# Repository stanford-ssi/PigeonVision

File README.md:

# PigeonVision

Video downlink for Stanford SSI's IREC rocket. Two fisheye cameras record the flight and send video to the ground for stitching and viewing.

Try the [flight demo](https://stanford-ssi.github.io/PigeonVision/) to see the camera views and stitched panorama.

**Current plan:** two IMX900 cameras at 30 fps, one CM5 and [Yapogee S3](hardware/yapogee-s3/README.md), an ESP32-S3-WROOM-1U DVB-S2 transmitter with RFFC5072A conversion from 2.42 GHz to 1.28 GHz. Keep Ethernet for an E200 fallback and a separate PA/filter board. The ESP32 path has conducted RF/video results; the new converter and PA chain still need schematic capture and hardware testing. Flight channel, bandwidth, power and ground receiver remain open.

- [Hardware](hardware/README.md): system diagram, carrier and RF frontend.
- [Yapogee S3](hardware/yapogee-s3/README.md): transmitter architecture, 5 V interface and waveform candidates.
- [Software](software/README.md): flight and ground tasks.
- [Link budget](calculations/link-budget.xlsx): RF and video bitrate calculations.
- [Simulator](docs/README.md): camera views, flight playback and local setup.

**Next:** capture and review the Yapogee S3 schematic, integrate the carrier interface and PA control, then complete layout and hardware qualification. The system, carrier, RF and software diagrams describe this plan; existing Pico transport measurements remain historical evidence.

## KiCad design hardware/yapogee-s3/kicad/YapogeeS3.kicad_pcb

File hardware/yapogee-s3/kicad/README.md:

# Yapogee S3 KiCad

Open [YapogeeS3.kicad_pro](YapogeeS3.kicad_pro) in KiCad 10. Placement, routing and ground stitching are captured. USB breakout and silkscreen DRC follow-up remains.

| Sheet | Main parts |
| --- | --- |
| Root | USB-C, TPD2EUSB30, CC resistors, JP1 and the castellated edge |
| MCU | WROOM-1U-N16R8, direct host bus, RF control translator, local BOOT/RESET and native USB |
| POWER | TPS62933FDRLR, SRP5030TA-2R2M, TPS7A9001DSKR, TPS22919DCKR |
| RF_FRONT_END | RFFC5072A, TCXO/reference buffer, baluns, filter, SPF5043Z and SMA |

[Design Master](../design-master.xlsx) · [Datasheet PDFs](../datasheets.md) · [BOM](../BOM.csv) · [Interfaces](../interfaces.md)

The project tables include local IO and Power libraries. The IO library includes the module-edge strip symbol, assigned to the paired header/castellation footprint with 12 extra GND anchors. Power rails use global symbols; hierarchy ports carry signals. The BOM covers the captured circuit. Numbering is retained during the direct-host change. GPIO2 is free and castellation 14 is reserved.

Power, direct host GPIO, RF control translation and MCU EN/reset/boot support are captured. RF capture includes matching, PLL loop, reference, supplies and driver. The RF sheet uses A3 for spacing. Design Master contains capacitor screens and loop-model estimates; hardware stability is unmeasured.

J1 carries the closed 55 × 43.18 mm Edge.Cuts outline, R1 outer corners and the Samtec drop-in notch. The 19 mm U.FL harness remains one arc on Dwgs.User. Headers sit 1.60 mm inboard with continuous oval copper lands; retain manual edge soldering and no carrier paste. The JLCPCB JLC04161H-7628 standard 1.6 mm four-layer stackup is entered: 1 oz outer copper, 0.5 oz inner copper.

JP2 BOOT and JP3 RESET are bare, normally-open PCB jumper pads. For manual download, close BOOT during reset. Leave both open for normal operation; briefly short RESET to pull EN to GND. Native USB provides the usual ESP flashing path, without a UART bridge or Pi BOOT control.

## RF and routing

| Network | Populated values |
| --- | --- |
| Input pad | 3 dB nominal; 300 / 18 / 300 |
| Balanced DC blocks | C32/C33 and C59/C60: 100 pF each |
| Mixer output feeds | L3/L4: 7.5 nH each, LQW15AN7N5G80D |
| Driver feed | L2: 100 nH |
| Frequency plan | 3700 MHz LO − 2420 MHz input = 1280 MHz output; spectrum inverted |

Matching uses nominal manufacturer port and passive models. Bias 6 input impedance is unknown; assembled matching, output power and EVM remain unmeasured. Keep balanced connections short and symmetric. L3/L4 may need tuning after assembly.

MODE uses a 10k pullup. EXT_LO and EXT_LO_DEC stay open with the internal LO. The reference divider is nominally 1.2 Vpp before REF_IN loading. The driver uses switched 3.328 V minus switch, resistor and choke drops. Its 3 V characterization is typical; gain, stability and EVM need measurement. [RF plots](../plots/README.md).

| Netclass | Width (mm) | Pair gap (mm) | Coplanar GND gap (mm) |
| --- | ---: | ---: | ---: |
| RF50 | 0.32 | — | 0.25 |
| USB90 | 0.235 | 0.15 | 0.25 |
| RF_MATCH | 0.20 | — | — |
| REF40 | 0.20 | — | — |

RF50 and USB90 use masked L1 traces over continuous L2 GND. Hold the listed GND gaps with the actual copper pours; netclass clearance is only a minimum. RF_MATCH marks short lumped-network connections, not controlled 100/200 Ω lines. Vendor geometry still requires fabrication/CAM confirmation. [Stackup](../stackup.json) · [JLC calculator](https://jlcpcb.com/pcb-impedance-calculator)

Continuous RF wires use automatic net names with explicit netclass patterns. Recheck assignments after reannotation. USB_P/N and MCU UD_P/N are recognized differential pairs on both sides of R3/R4. REF40 is a short clock interconnect default, without an impedance target. Bypass captions assign each capacitor pair to its physical supply pin.

[JLC fabrication and routing rules](YapogeeS3.kicad_dru) are loaded with RF50, RF_MATCH, REF40, USB90 and power netclasses. RF50 and USB90 have explicit 0.25 mm clearance to GND. USB retains 0.15 mm pair spacing. Standard through vias only; USB breakout spacing and small existing silk still need DRC review.

Use netclass widths. Supply defaults are 0.75 mm for 5 V, 0.50 mm for 3V3_MAIN and 0.30 mm for RF/driver supplies; use pours where practical. These widths are starting values, not current or thermal qualifications. Default vias are 0.60/0.30 mm. New zones use netclass clearances; maintain the calculated 0.25 mm GND gaps along RF50 and USB90.

Ground stitching uses 0.50/0.20 mm vias across the board, with closer placement along RF paths and the shield. Minimum via diameter is 0.45 mm with a 0.125 mm annulus; via-to-via hole spacing is 0.20 mm. Component-hole spacing remains 0.45 mm. Refill and rerun DRC after routing changes. Stitch placement is not an EM validation.

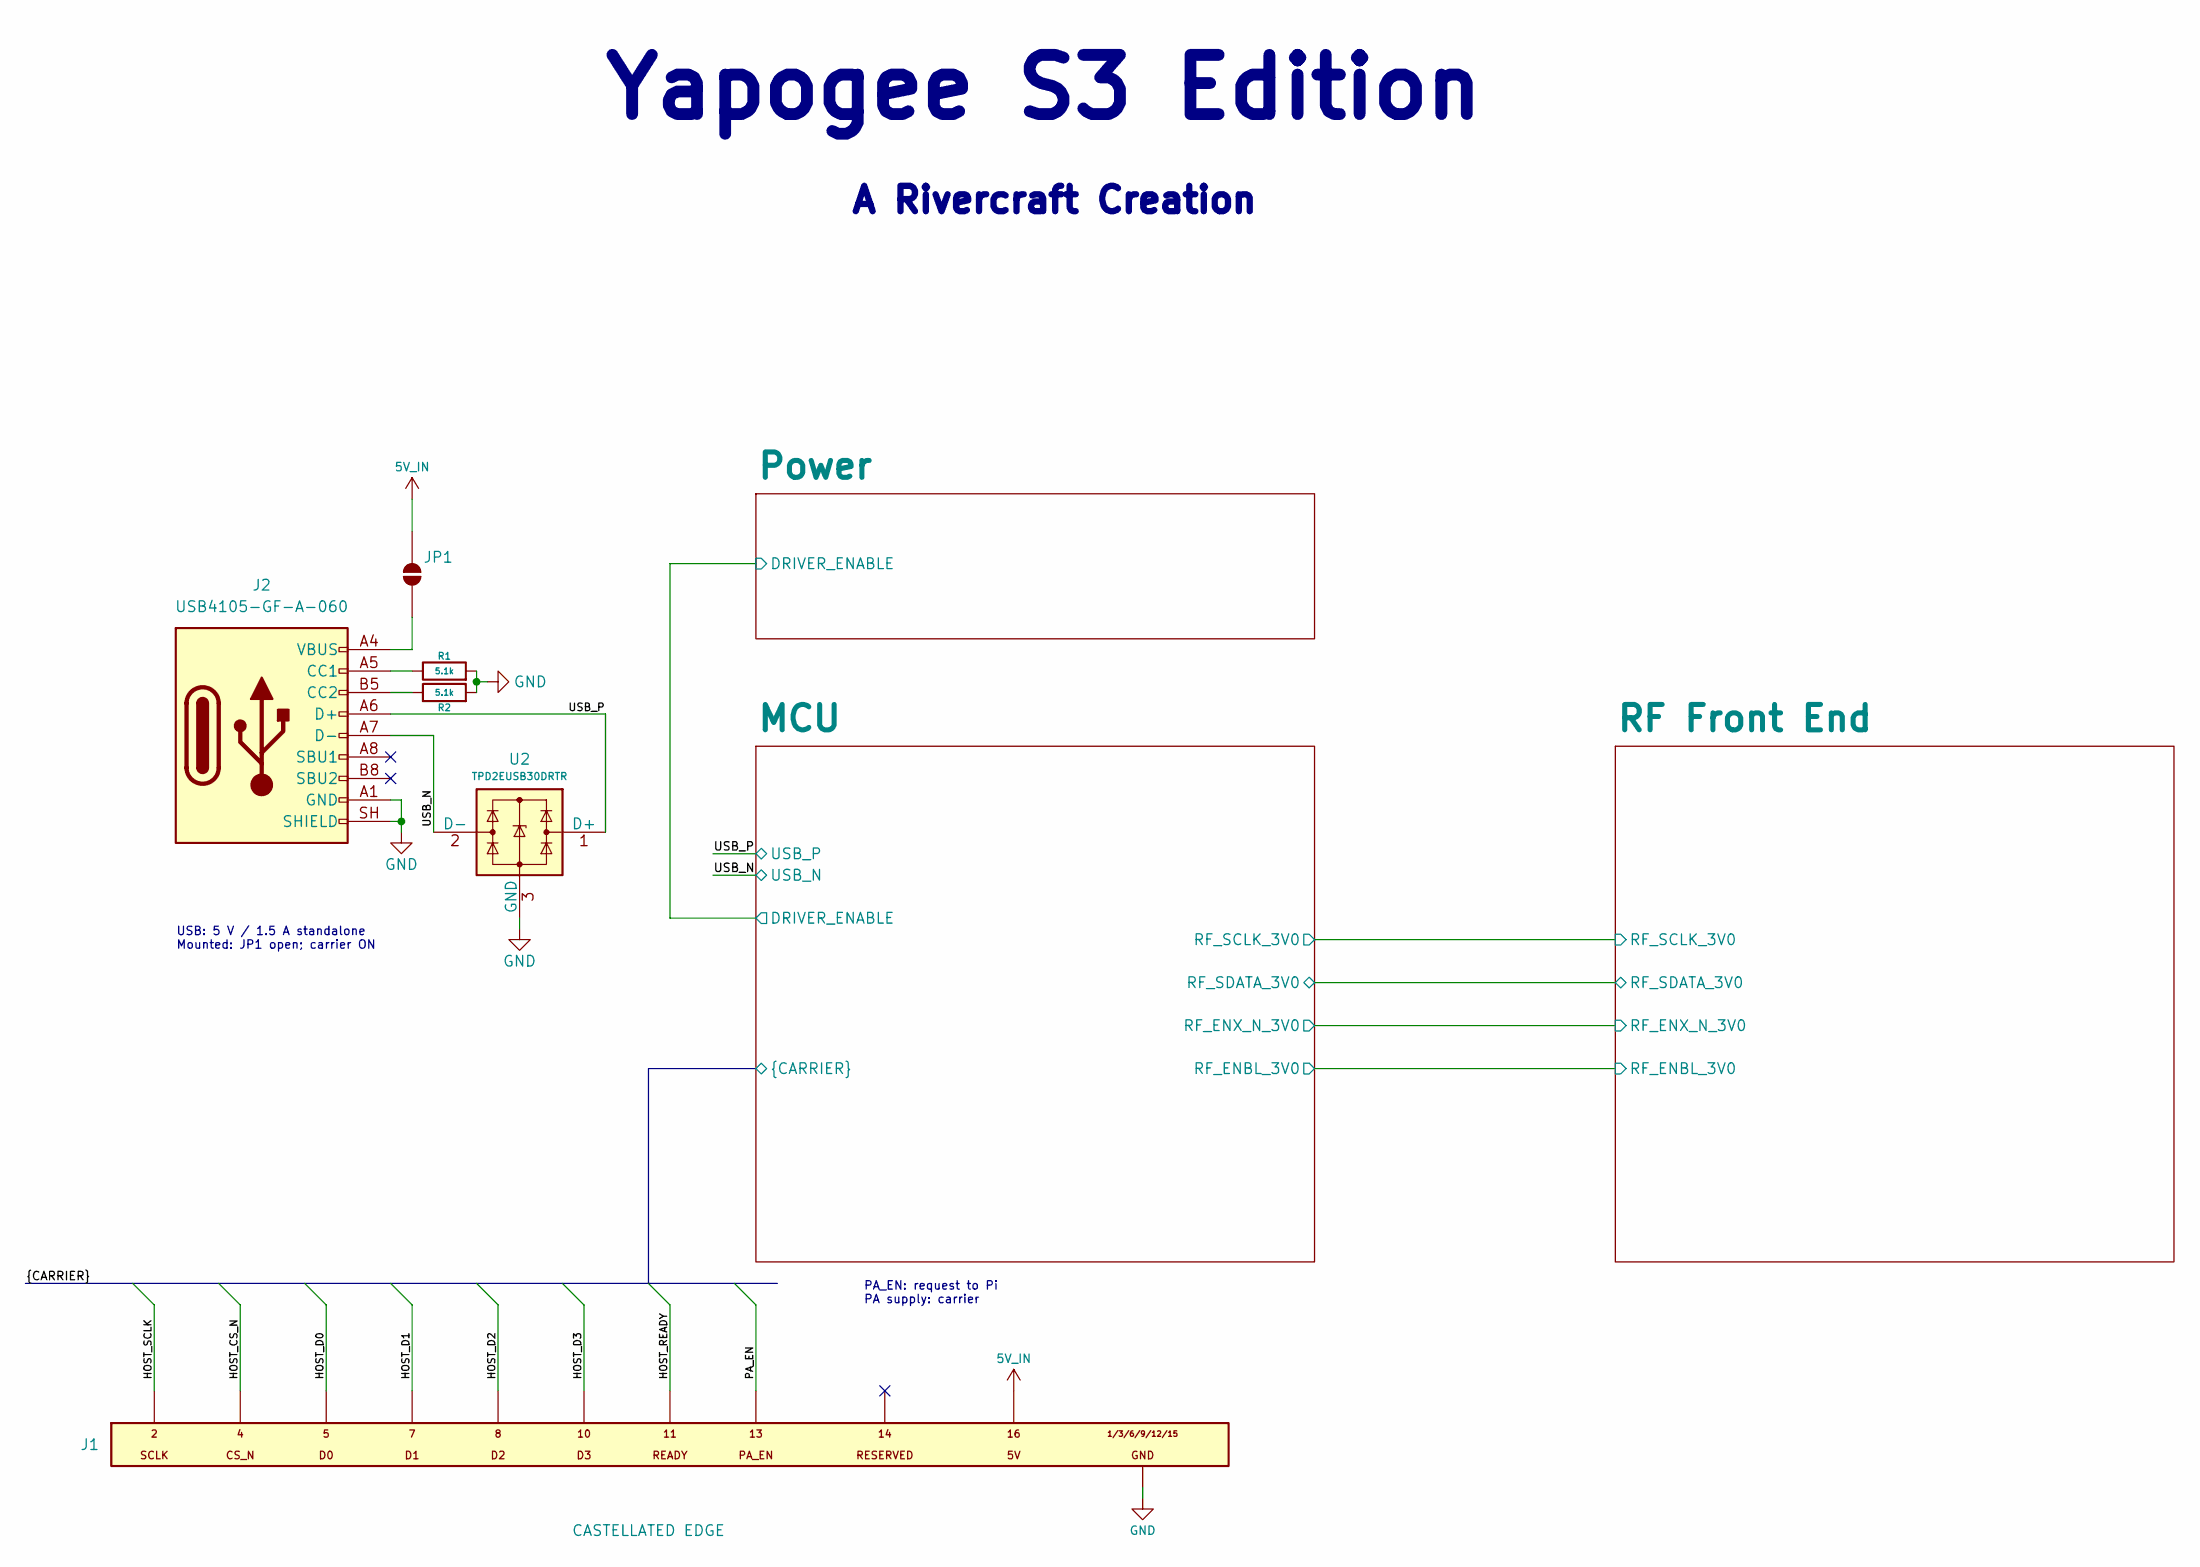
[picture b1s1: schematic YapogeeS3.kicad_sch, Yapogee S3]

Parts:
J1: CASTELLATED EDGE; YapogeeS3_Edge_Header16_55x43p18_P2p54_GND12
J2: USB4105-GF-A-060; USB_C_Receptacle_GCT_USB4105_GF_A_16P; MPN USB4105-GF-A-060
JP1: USB_PWR_LINK; SolderJumper_2_P1.3mm_Open
R1, R2: 5.1k; KiCad_Resistor_SMD_R_0402_1005Metric; MPN RC0402FR-075K1L
U2: TPD2EUSB30DRTR; TI_DRT0003A_TPD2EUSB30; MPN TPD2EUSB30DRTR

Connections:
5V_IN: J1.3 (5V), JP1.2 (B); also elsewhere on the board
/HOST_CS_N: J1.4 (CS_N); also elsewhere on the board
/HOST_D0: J1.5 (D0); also elsewhere on the board
/HOST_D1: J1.7 (D1); also elsewhere on the board
/HOST_D2: J1.8 (D2); also elsewhere on the board
/HOST_D3: J1.10 (D3); also elsewhere on the board
/HOST_READY: J1.11 (READY); also elsewhere on the board
/HOST_SCLK: J1.2 (SCLK); also elsewhere on the board
/PA_EN: J1.13 (PA_EN); also elsewhere on the board
/USB_N: J2.A7 (D-), J2.B7 (D-), U2.2 (D-); also elsewhere on the board
/USB_P: J2.A6 (D+), J2.B6 (D+), U2.1 (D+); also elsewhere on the board
GND: J1.1 (GND), J1.6 (GND), J1.9 (GND), J1.12 (GND), J1.15 (GND), J1.16 (GND), J2.A1 (GND), J2.A12 (GND), J2.B1 (GND), J2.B12 (GND), J2.SH (SHIELD), R1.2, R2.2, U2.3 (GND); also elsewhere on the board
unnamed: J2.A5 (CC1), R1.1
unnamed: J2.B5 (CC2), R2.1
unnamed: J2.A4 (VBUS), J2.A9 (VBUS), J2.B4 (VBUS), J2.B9 (VBUS), JP1.1 (A)

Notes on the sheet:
PA_EN: request to Pi PA supply: carrier
A Rivercraft Creation
Yapogee S3 Edition
USB: 5 V / 1.5 A standalone Mounted: JP1 open; carrier ON

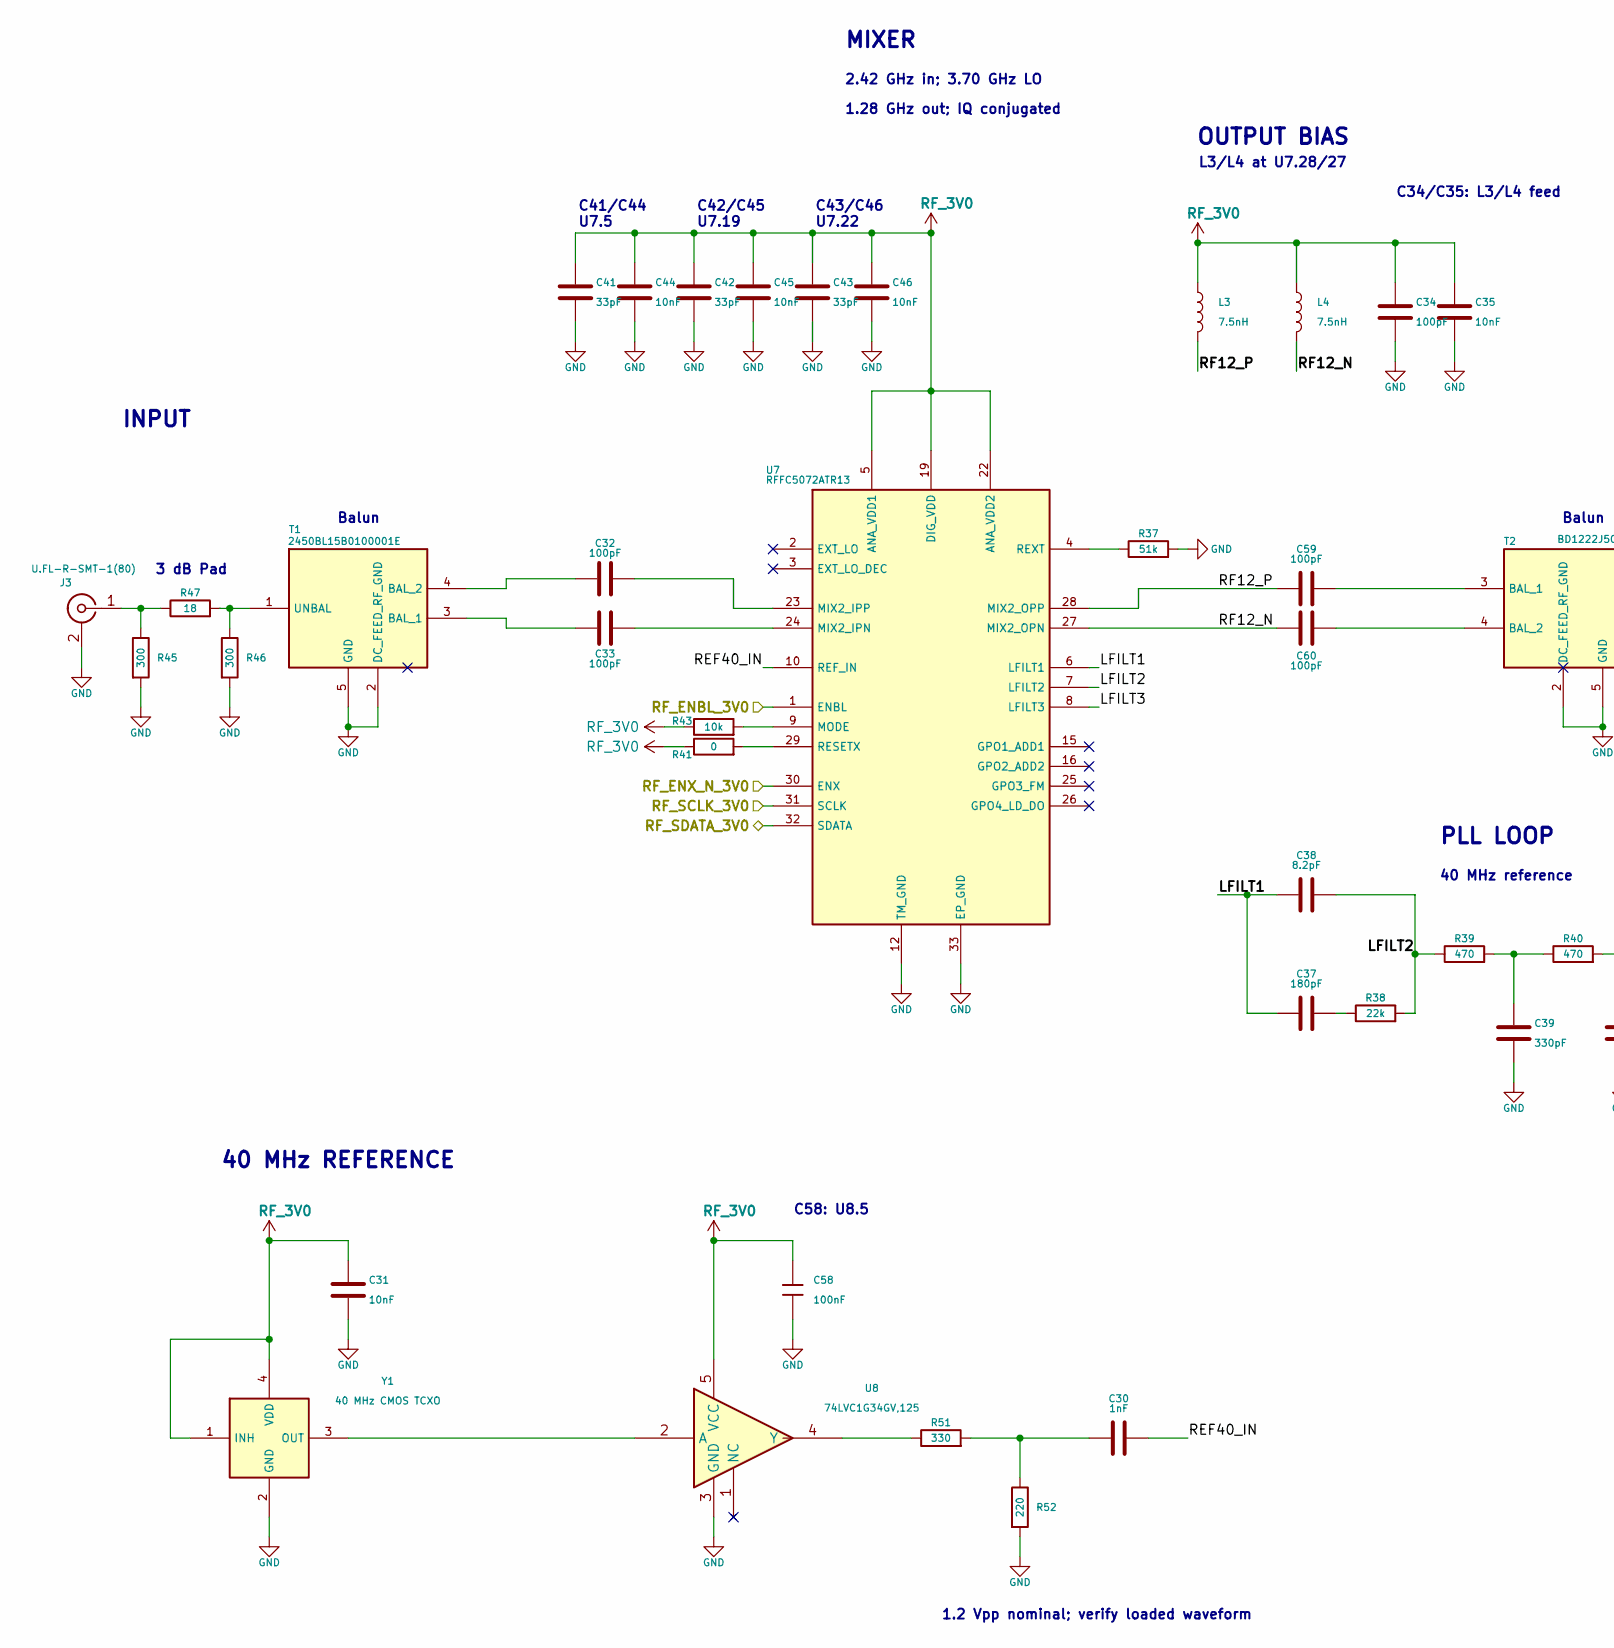
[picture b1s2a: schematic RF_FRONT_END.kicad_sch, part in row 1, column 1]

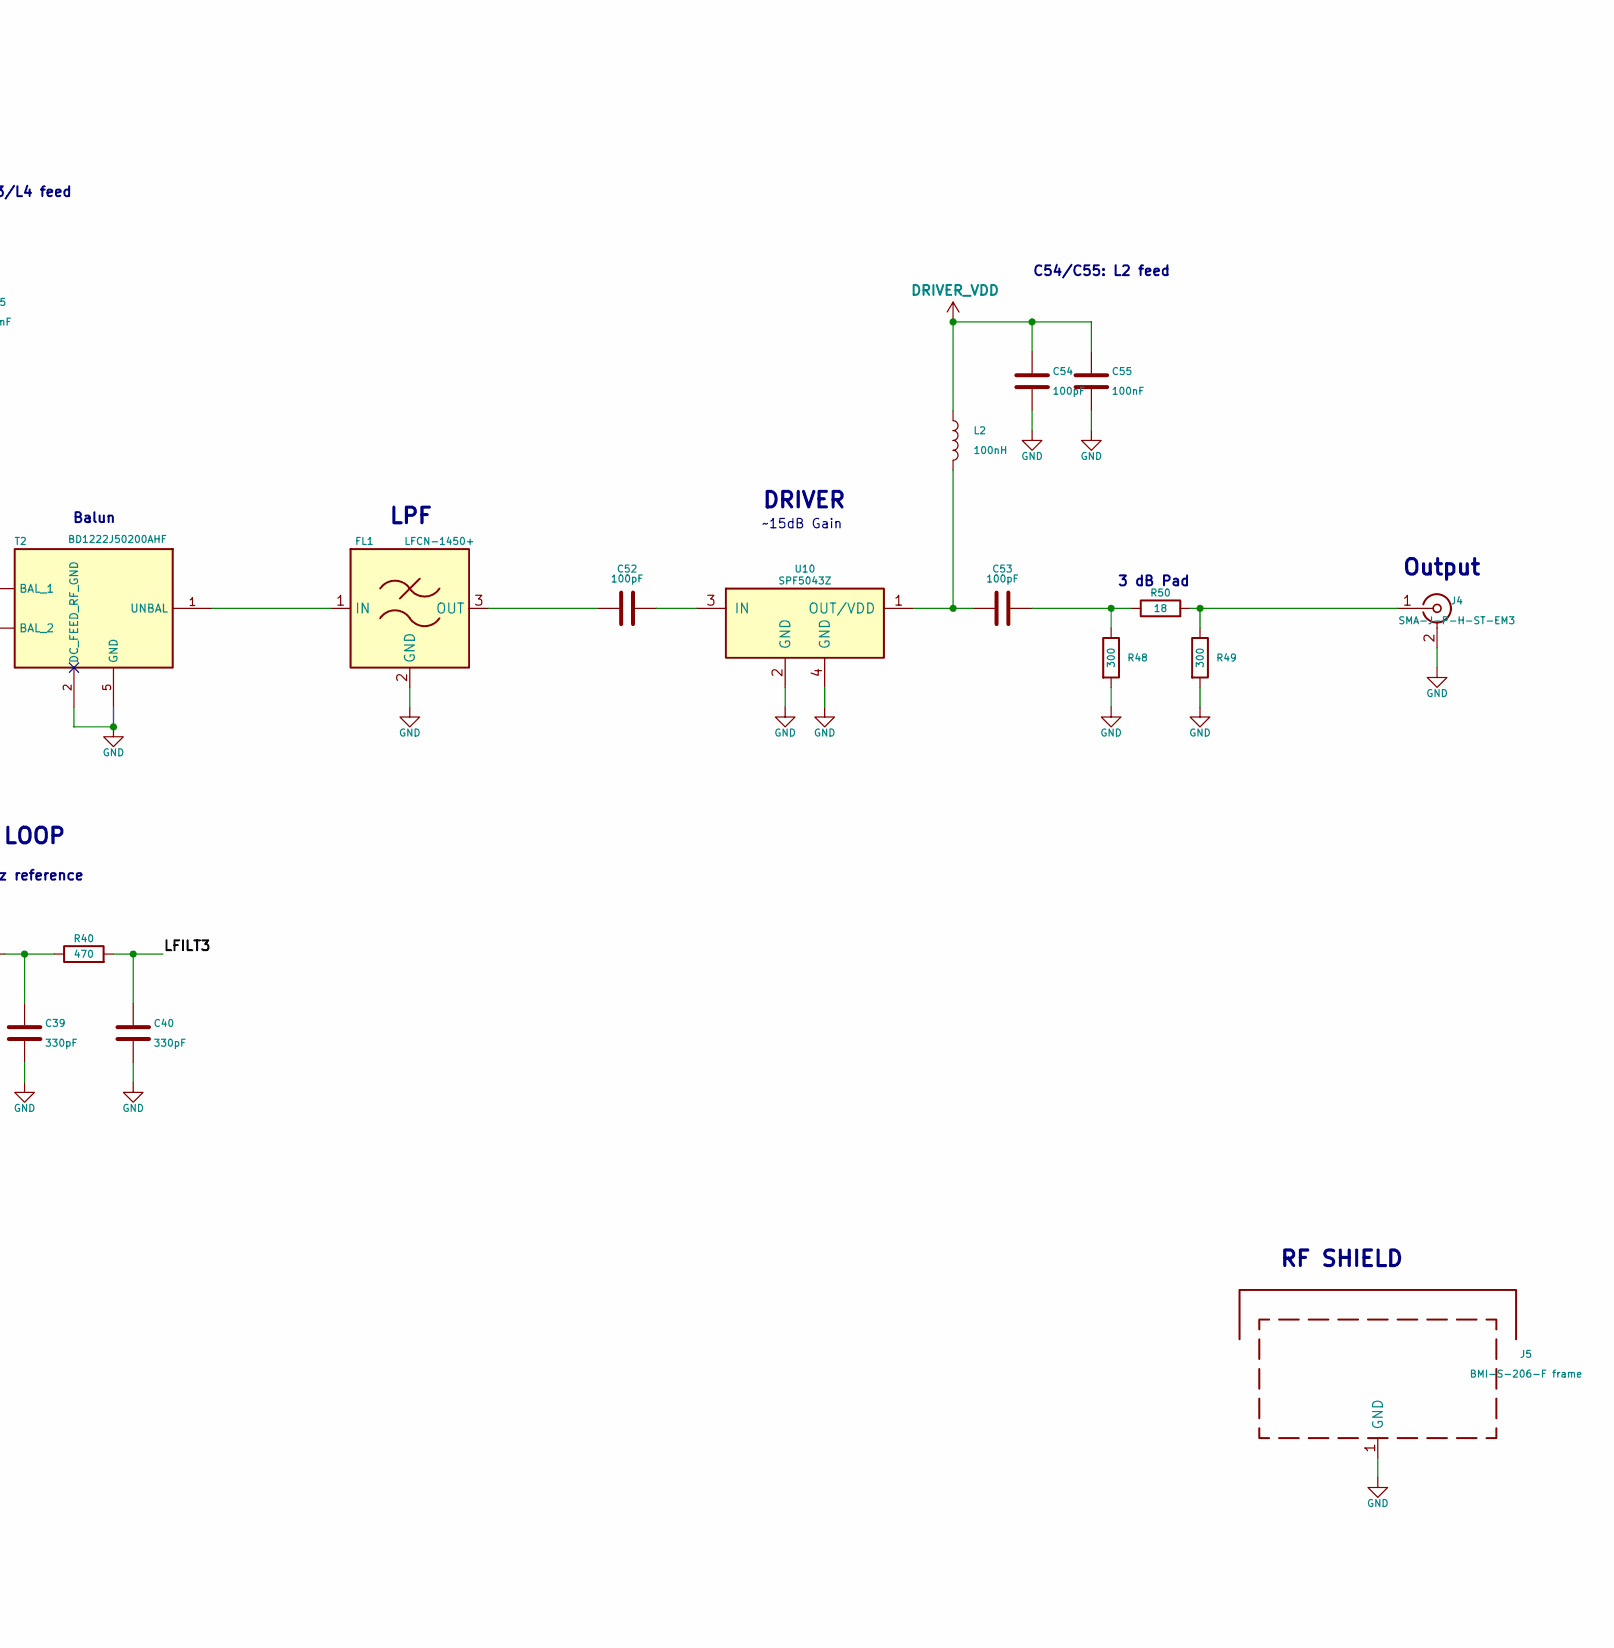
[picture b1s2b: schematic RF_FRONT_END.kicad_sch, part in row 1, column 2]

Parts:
C30: 1nF; KiCad_Capacitor_SMD_C_0402_1005Metric; MPN GRM1555C1H102JA01D
C31, C35, C44, C45, C46: 10nF; KiCad_Capacitor_SMD_C_0402_1005Metric; MPN GRM155R71C103KA01D
C32, C33, C34, C59, C60: 100pF; KiCad_Capacitor_SMD_C_0402_1005Metric; MPN GRM1555C1H101JA01D
C37: 180pF; KiCad_Capacitor_SMD_C_0402_1005Metric; MPN GRM1555C1H181JA01D
C38: 8.2pF; KiCad_Capacitor_SMD_C_0402_1005Metric; MPN GRM1555C1H8R2DA01D
C39, C40: 330pF; KiCad_Capacitor_SMD_C_0402_1005Metric; MPN GRM1555C1H331JA01D
C41, C42, C43: 33pF; KiCad_Capacitor_SMD_C_0402_1005Metric; MPN GRM1555C1H330JA01D
C52, C53, C54: 100pF; KiCad_Capacitor_SMD_C_0603_1608Metric; MPN GRM1885C1H101JA01D
C55: 100nF; KiCad_Capacitor_SMD_C_0603_1608Metric; MPN GRM188R72A104KA35D
C58: 100nF; C_Murata_GCM15_1005_RefReflow; Voltage Rated 50V; Tolerance ±10%; MPN GCM155R71H104KE02D; LCSC C85858
FL1: LFCN-1450+; Filter_Mini-Circuits_FV1206; MPN LFCN-1450+
J3: U.FL-R-SMT-1(80); Hirose_U_FL_R_SMT_1_80_HandSolder; MPN U.FL-R-SMT-1(80)
J4: SMA-J-P-H-ST-EM3; Samtec_SMA_J_P_H_ST_EM3_DropInEdge; MPN SMA-J-P-H-ST-EM3
J5: BMI-S-206-F frame; KiCad_RF_Shielding_Laird_Technologies_BMI-S-206-F_36.83x33.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; MPN BMI-S-206-F
L2: 100nH; Murata_LQW18AN_00_1608; MPN LQW18ANR10J00D
L3, L4: 7.5nH; Murata_LQW15AN_80_1006; MPN LQW15AN7N5G80D
R37: 51k; KiCad_Resistor_SMD_R_0402_1005Metric; MPN RC0402FR-0751KL
R38: 22k; KiCad_Resistor_SMD_R_0402_1005Metric; MPN RC0402FR-0722KL
R39, R40: 470; KiCad_Resistor_SMD_R_0402_1005Metric; MPN RC0402FR-07470RL
R41: 0; KiCad_Resistor_SMD_R_0402_1005Metric; MPN RC0402JR-070RL
R43: 10k; KiCad_Resistor_SMD_R_0402_1005Metric; MPN RC0402FR-0710KL
R45, R46, R48, R49: 300; KiCad_Resistor_SMD_R_0402_1005Metric; MPN RC0402FR-07300RL
R47, R50: 18; KiCad_Resistor_SMD_R_0402_1005Metric; MPN RC0402FR-0718RL
R51: 330; KiCad_Resistor_SMD_R_0402_1005Metric; MPN RC0402FR-07330RL
R52: 220; KiCad_Resistor_SMD_R_0402_1005Metric; MPN RC0402FR-07220RL
T1: 2450BL15B0100001E; Johanson_2450BL15B_6Pad_2x1.25; MPN 2450BL15B0100001E
T2: BD1222J50200AHF; TTM_BD1222J50200AHF_6Pad_2.04x1.29; MPN BD1222J50200AHF
U7: RFFC5072ATR13; RFFC5072A_QFN32_5x5_EP3.7; MPN RFFC5072ATR13
U8: 74LVC1G34GV,125; KiCad_Package_TO_SOT_SMD_SOT-23-5; MPN 74LVC1G34GV,125
U10: SPF5043Z; Qorvo_SPF5043Z_SOT343_WideGND; MPN SPF5043Z
Y1: 40 MHz CMOS TCXO; Abracon_ATXAIG_H13_2016_4Pad; MPN ATXAIG-H13-F-40.000MHZ-F25-T3

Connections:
/MCU/RF_ENBL_3V0: U7.1 (ENBL); also elsewhere on the board
/MCU/RF_ENX_N_3V0: U7.30 (ENX); also elsewhere on the board
/MCU/RF_SCLK_3V0: U7.31 (SCLK); also elsewhere on the board
/MCU/RF_SDATA_3V0: U7.32 (SDATA); also elsewhere on the board
/RF Front End/LFILT1: C37.1, C38.1, U7.6 (LFILT1)
/RF Front End/LFILT2: C38.2, R38.2, R39.1, U7.7 (LFILT2)
/RF Front End/LFILT3: C40.1, R40.2, U7.8 (LFILT3)
/RF Front End/REF40_IN: C30.2, U7.10 (REF_IN)
/RF Front End/RF12_N: C60.1, L4.2, U7.27 (MIX2_OPN)
/RF Front End/RF12_P: C59.1, L3.2, U7.28 (MIX2_OPP)
DRIVER_VDD: C54.1, C55.1, L2.1; also elsewhere on the board
GND: C31.2, C34.2, C35.2, C39.2, C40.2, C41.2, C42.2, C43.2, C44.2, C45.2, C46.2, C54.2, C55.2, C58.2, FL1.2 (GND), FL1.4 (GND), J3.2 (Ext), J4.2 (Ext), J5.1 (GND_1), R37.2, R45.2, R46.2, R48.2, R49.2, R52.2, T1.2 (DC_FEED_RF_GND), T1.5 (GND), T2.2 (DC_FEED_RF_GND), T2.5 (GND), U7.12 (TM_GND), U7.33 (EP_GND), U8.3 (GND), U10.2 (GND), U10.4 (GND), Y1.2 (GND); also elsewhere on the board
unnamed: C30.1, R51.2, R52.1
unnamed: C37.2, R38.1
unnamed: C39.1, R39.2, R40.1
unnamed: C53.2, R48.1, R50.1
unnamed: FL1.1 (IN), T2.1 (UNBAL)
unnamed: C52.1, FL1.3 (OUT)
unnamed: J3.1 (In), R45.1, R47.1
unnamed: J4.1 (In), R49.1, R50.2
unnamed: C33.1, T1.3 (BAL_1)
unnamed: C32.1, T1.4 (BAL_2)
unnamed: R46.1, R47.2, T1.1 (UNBAL)
unnamed: C59.2, T2.3 (BAL_1)
unnamed: C60.2, T2.4 (BAL_2)
unnamed: C33.2, U7.24 (MIX2_IPN)
unnamed: C32.2, U7.23 (MIX2_IPP)
unnamed: R43.2, U7.9 (MODE)
unnamed: R41.2, U7.29 (RESETX)
unnamed: R37.1, U7.4 (REXT)
unnamed: U8.2 (A), Y1.3 (OUT)
unnamed: R51.1, U8.4 (Y)
unnamed: C52.2, U10.3 (IN)
unnamed: C53.1, L2.2, U10.1 (OUT/VDD)
RF_3V0: C31.1, C34.1, C35.1, C41.1, C42.1, C43.1, C44.1, C45.1, C46.1, C58.1, L3.1, L4.1, R41.1, R43.1, U7.5 (ANA_VDD1), U7.19 (DIG_VDD), U7.22 (ANA_VDD2), U8.5 (VCC), Y1.1 (INH), Y1.4 (VDD); also elsewhere on the board

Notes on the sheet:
~15dB Gain
Output
1.2 Vpp nominal; verify loaded waveform
C42/C45 U7.19
MIXER
Balun
C43/C46 U7.22
LPF
3 dB Pad
40 MHz reference
C54/C55: L2 feed
DRIVER
C58: U8.5
PLL LOOP
L3/L4 at U7.28/27
2.42 GHz in; 3.70 GHz LO
RF SHIELD
OUTPUT BIAS
C41/C44 U7.5
40 MHz REFERENCE
C34/C35: L3/L4 feed
INPUT
1.28 GHz out; IQ conjugated

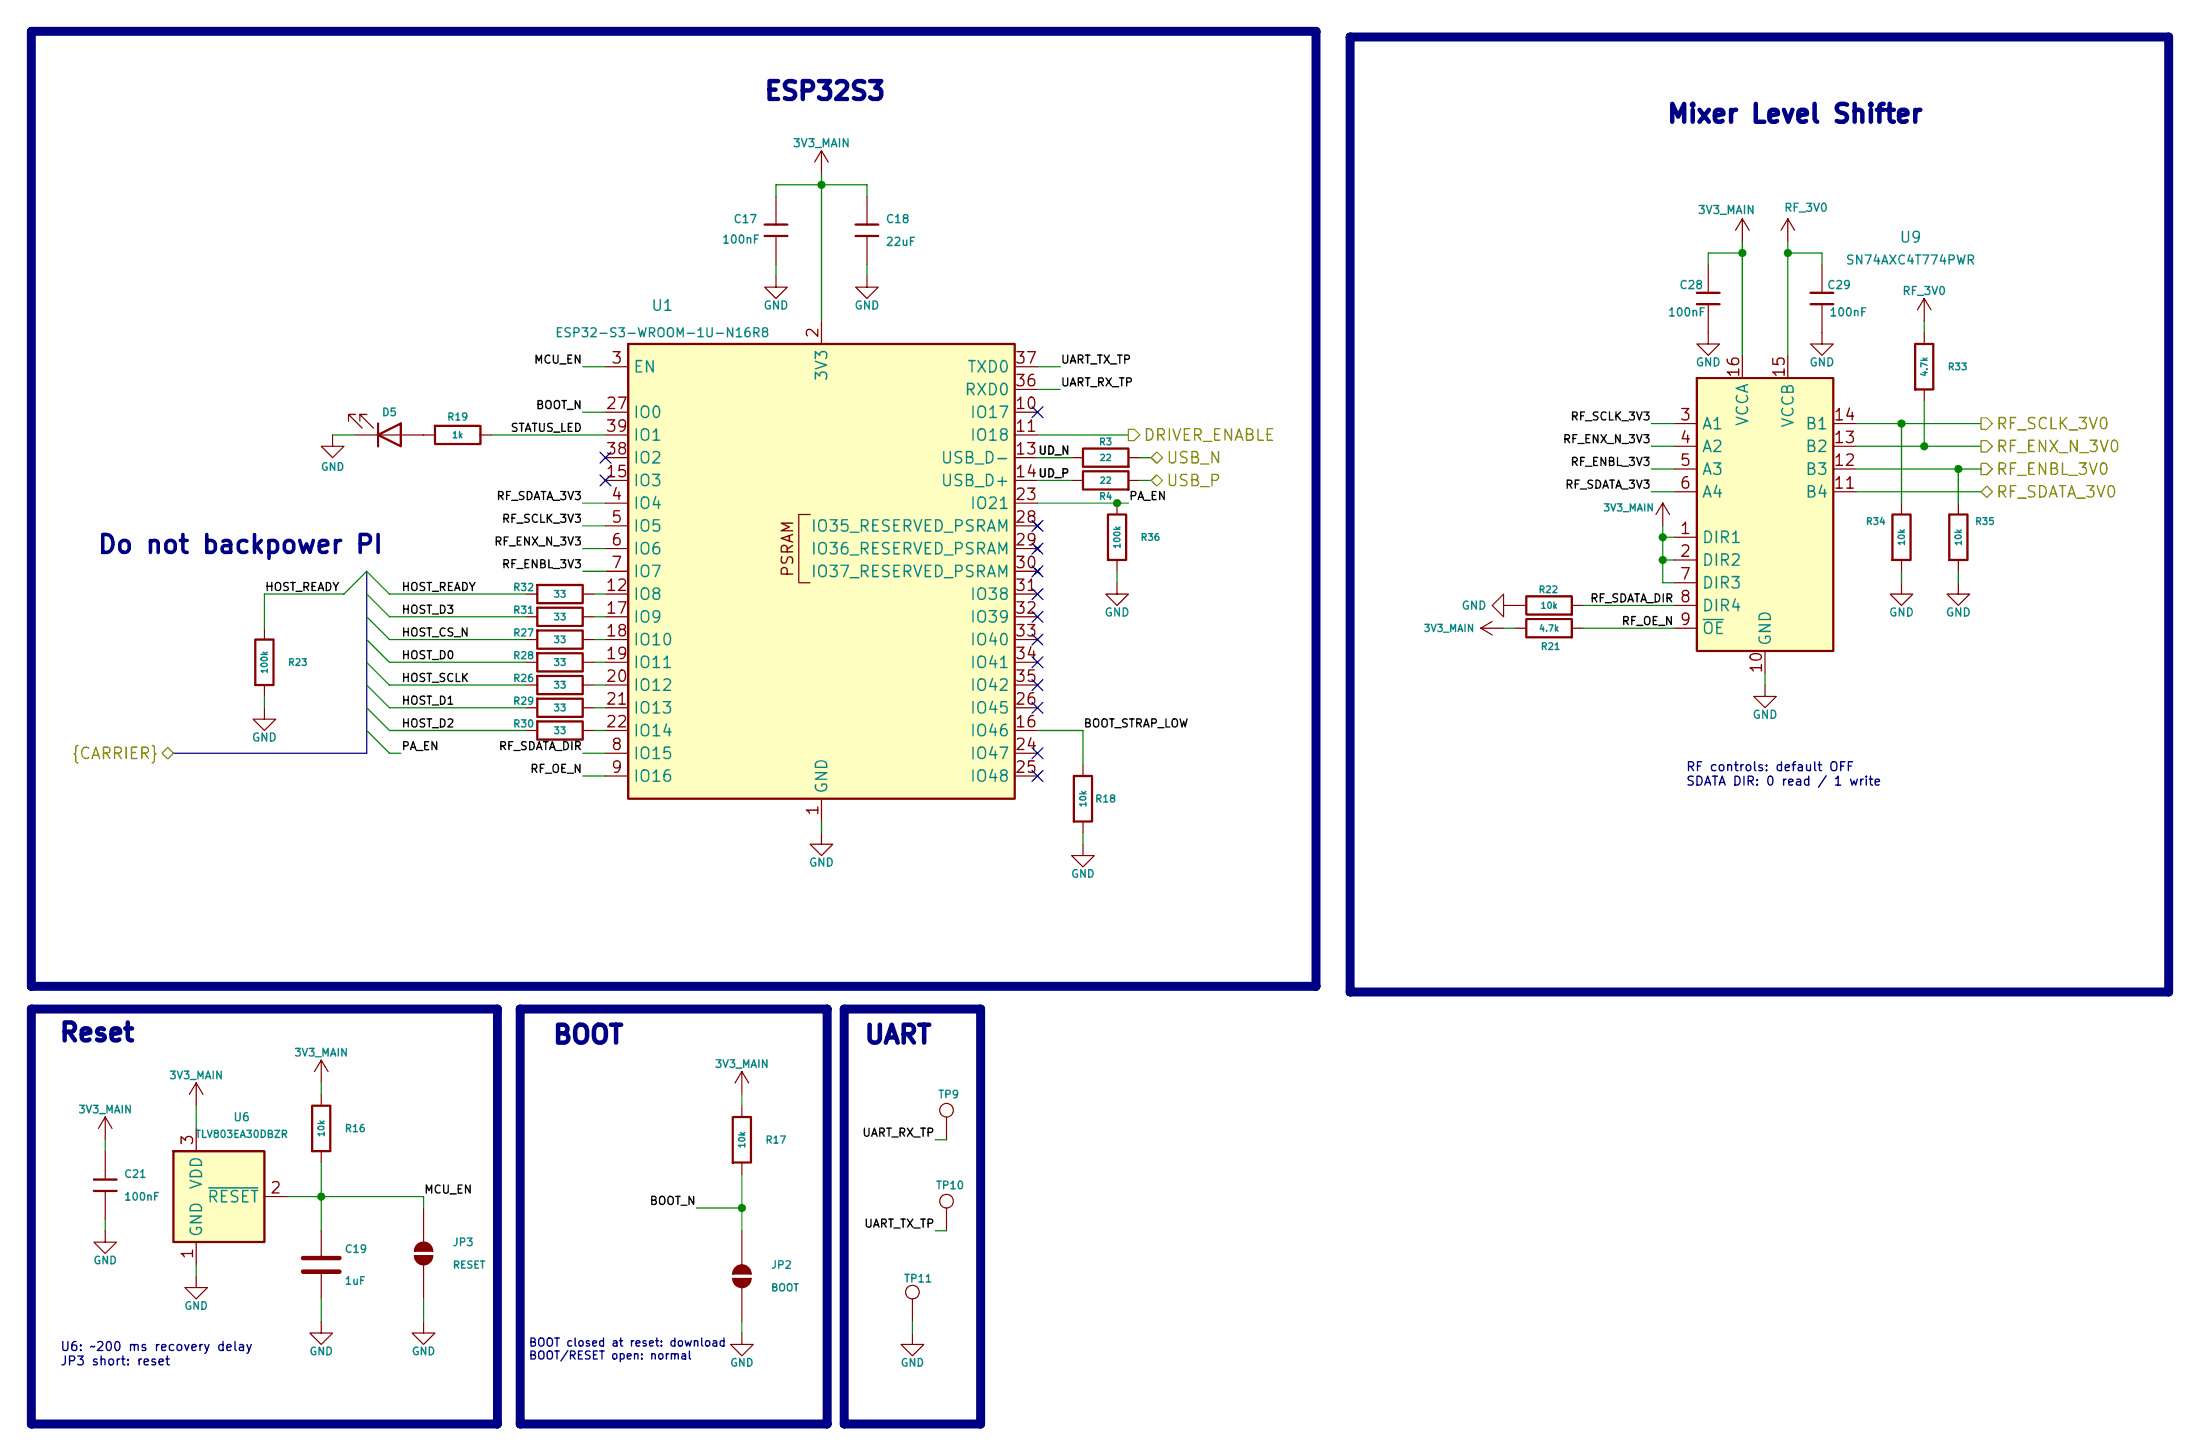
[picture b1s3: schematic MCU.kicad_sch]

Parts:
C17, C21, C28, C29: 100nF; C_Murata_GCM15_1005_RefReflow; Voltage Rated 50V; Tolerance ±10%; MPN GCM155R71H104KE02D; LCSC C85858
C18: 22uF; C_Murata_GCM31_3216_RefReflow; Voltage Rated 10V; Tolerance ±10%; MPN GCM31CR71A226KE02L; LCSC C126598
C19: 1uF; KiCad_Capacitor_SMD_C_0603_1608Metric; MPN C1608X7R1C105K080AC
D5: LTST-C170KGKT; LiteOn_LTST-C170KGKT_0805; MPN LTST-C170KGKT; DigiKey Part # 160-1414-1-ND
JP2: BOOT; SolderJumper_2_P1.3mm_Open; MPN PCB_SOLDER_JUMPER_2_OPEN
JP3: RESET; SolderJumper_2_P1.3mm_Open; MPN PCB_SOLDER_JUMPER_2_OPEN
R3, R4: 22; KiCad_Resistor_SMD_R_0402_1005Metric; MPN RC0402FR-0722RL
R16, R17, R18, R22, R34, R35: 10k; KiCad_Resistor_SMD_R_0402_1005Metric; MPN RC0402FR-0710KL
R19: 1k; KiCad_Resistor_SMD_R_0402_1005Metric; MPN RC0402FR-071KL
R21, R33: 4.7k; KiCad_Resistor_SMD_R_0402_1005Metric; MPN RC0402FR-074K7L
R23, R36: 100k; KiCad_Resistor_SMD_R_0402_1005Metric; MPN RC0402FR-07100KL
R26, R27, R28, R29, R30, R31, R32: 33; KiCad_Resistor_SMD_R_0402_1005Metric; MPN RC0402FR-0733RL
TP9: UART_RX_TP; TestPoint_Pad_D1.0mm; MPN PCB_TEST_PAD_1MM
TP10: UART_TX_TP; TestPoint_Pad_D1.0mm; MPN PCB_TEST_PAD_1MM
TP11: GND; TestPoint_Pad_D1.0mm; MPN PCB_TEST_PAD_1MM
U1: ESP32-S3-WROOM-1U-N16R8; Espressif_ESP32_S3_WROOM_1U_18x19.2mm; MPN ESP32-S3-WROOM-1U-N16R8
U6: TLV803EA30DBZR; TI_DBZ0003A_TLV803E; MPN TLV803EA30DBZR
U9: SN74AXC4T774PWR; TI_PW0016A_SN74AXC4T774; MPN SN74AXC4T774PWR

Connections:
3V3_MAIN: C17.1, C18.1, C21.1, C28.1, R16.1, R17.1, R21.1, U1.2 (3V3), U6.3 (VDD), U9.1 (DIR1), U9.2 (DIR2), U9.7 (DIR3), U9.16 (VCCA); also elsewhere on the board
/HOST_CS_N: R27.2; also elsewhere on the board
/HOST_D0: R28.2; also elsewhere on the board
/HOST_D1: R29.2; also elsewhere on the board
/HOST_D2: R30.2; also elsewhere on the board
/HOST_D3: R31.2; also elsewhere on the board
/HOST_READY: R23.1, R32.2; also elsewhere on the board
/HOST_SCLK: R26.2; also elsewhere on the board
/MCU/BOOT_N: JP2.1 (A), R17.2, U1.27 (IO0)
/MCU/BOOT_STRAP_LOW: R18.1, U1.16 (IO46)
/MCU/DRIVER_ENABLE: U1.11 (IO18); also elsewhere on the board
/MCU/MCU_EN: C19.1, JP3.1 (A), R16.2, U1.3 (EN), U6.2 (~RESET)
/MCU/RF_ENBL_3V0: R35.1, U9.12 (B3); also elsewhere on the board
/MCU/RF_ENBL_3V3: U1.7 (IO7), U9.5 (A3)
/MCU/RF_ENX_N_3V0: R33.2, U9.13 (B2); also elsewhere on the board
/MCU/RF_ENX_N_3V3: U1.6 (IO6), U9.4 (A2)
/MCU/RF_OE_N: R21.2, U1.9 (IO16), U9.9 (~OE)
/MCU/RF_SCLK_3V0: R34.1, U9.14 (B1); also elsewhere on the board
/MCU/RF_SCLK_3V3: U1.5 (IO5), U9.3 (A1)
/MCU/RF_SDATA_3V0: U9.11 (B4); also elsewhere on the board
/MCU/RF_SDATA_3V3: U1.4 (IO4), U9.6 (A4)
/MCU/RF_SDATA_DIR: R22.2, U1.8 (IO15), U9.8 (DIR4)
/MCU/STATUS_LED: R19.1, U1.39 (IO1)
/MCU/UART_RX_TP: TP9.1 (1_1), U1.36 (RXD0)
/MCU/UART_TX_TP: TP10.1 (1_1), U1.37 (TXD0)
/MCU/UD_N: R3.1, U1.13 (USB_D-)
/MCU/UD_P: R4.1, U1.14 (USB_D+)
/PA_EN: R36.1, U1.23 (IO21); also elsewhere on the board
/USB_N: R3.2; also elsewhere on the board
/USB_P: R4.2; also elsewhere on the board
GND: C17.2, C18.2, C19.2, C21.2, C28.2, C29.2, D5.1 (K), JP2.2 (B), JP3.2 (B), R18.2, R22.1, R23.2, R34.2, R35.2, R36.2, TP11.1 (1_1), U1.1 (GND), U1.40 (GND), U1.41 (GND), U6.1 (GND), U9.10 (GND); also elsewhere on the board
unnamed: D5.2 (A), R19.2
unnamed: R32.1, U1.12 (IO8)
unnamed: R31.1, U1.17 (IO9)
unnamed: R27.1, U1.18 (IO10)
unnamed: R28.1, U1.19 (IO11)
unnamed: R26.1, U1.20 (IO12)
unnamed: R29.1, U1.21 (IO13)
unnamed: R30.1, U1.22 (IO14)
RF_3V0: C29.1, R33.1, U9.15 (VCCB); also elsewhere on the board

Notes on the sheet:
Mixer Level Shifter
Do not backpower PI
ESP32S3
BOOT closed at reset: download BOOT/RESET open: normal
BOOT
RF controls: default OFF SDATA DIR: 0 read / 1 write
Reset
U6: ~200 ms recovery delay JP3 short: reset
UART
